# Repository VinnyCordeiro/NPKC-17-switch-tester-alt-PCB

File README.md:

# NPKC 17 Switch Tester alternative PCB
Alternative PCB to convert the NPKC 17 switch tester (https://www.massdrop.com/buy/npkc-switch-tester?mode=guest_open or https://www.massdrop.com/buy/npkc-17-switch-tester?mode=guest_open) into a number pad. It is small enough to be modified by the free version of [EAGLE](https://cadsoft.io/). You can buy the PCB through [Dirty PCBs](https://dirtypcbs.com/store/designer/details/9479/676/aunk-numpad).

The Atmel ATmega32U2 microcontroller can be programmed with both [TMK keyboard firmware](https://github.com/tmk/tmk_keyboard) and [QMK keyboard firmware](https://github.com/qmk/qmk_firmware). TMK code for this PCB can be found [here](https://github.com/VinnyCordeiro/tmk_keyboard/tree/master/keyboard/AUNK_Numpad), while the QMK code (and a standard number pad firmware) is now available here.

As of September 08, 2020, the design is still untested.

Updates
-------
#### 13/September/2016
Initial release. Included are all custom libraries for EAGLE.

#### 15/January/2019
Uploaded a tentative firmware made with the help of [Keyboard Firmware Builder](https://kbfirmware.com/). Design still untested.

#### 08/September/2020
Remebered to add the link for people to buy the PCB. Design still untested (I'm off from the mechanical keyboards hobby for personal reasons).

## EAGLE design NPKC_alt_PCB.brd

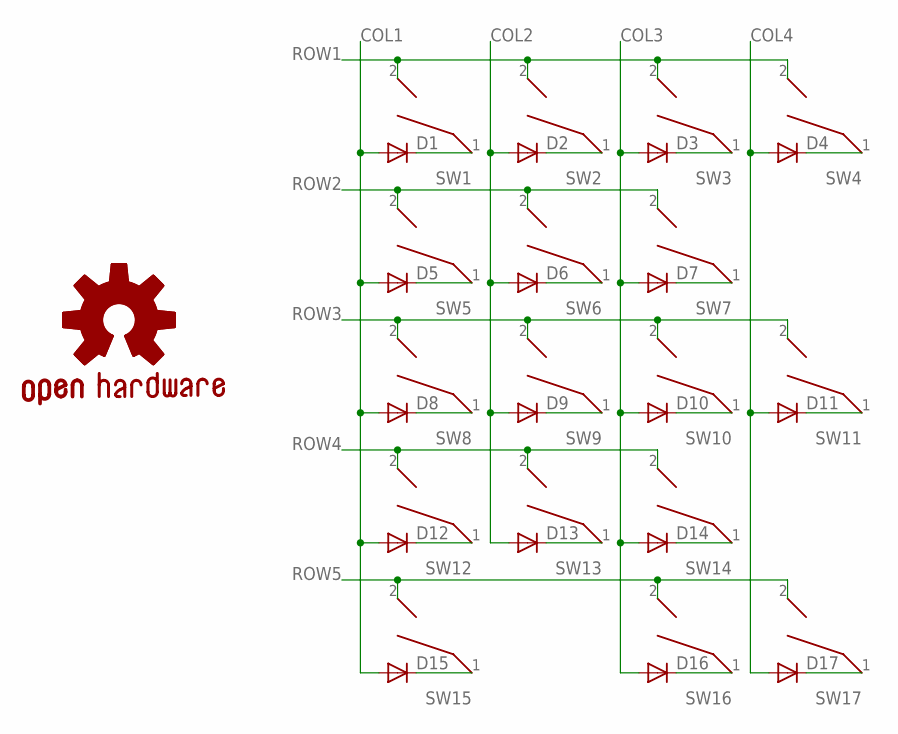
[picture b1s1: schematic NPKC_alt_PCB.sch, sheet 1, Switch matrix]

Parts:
D1, D2, D3, D4, D5, D6, D7, D8, D9, D10, D11, D12, D13, D14, D15, D16, D17: CGRM4001-G; SOD-123_MINI-SMA
GOLD_ORB_SM1: OSHWLOGO_GOLD_ORB_SM; OSHW2
SW1: Num_Lock; MX1A-XXNW
SW2: NP_/; MX1A-XXNW
SW3: NP_*; MX1A-XXNW
SW4: NP_-; MX1A-XXNW
SW5: NP_7; MX1A-XXNW
SW6: NP_8; MX1A-XXNW
SW7: NP_9; MX1A-XXNW
SW8: NP_4; MX1A-XXNW
SW9: NP_5; MX1A-XXNW
SW10: NP_6; MX1A-XXNW
SW11: NP_+; MX1A-XXNW
SW12: NP_1; MX1A-XXNW
SW13: NP_2; MX1A-XXNW
SW14: NP_3; MX1A-XXNW
SW15: NP_0; MX1A-XXNW
SW16: NP_.; MX1A-XXNW
SW17: NP_Enter; MX1A-XXNW

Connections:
COL1: D1.A, D5.A, D8.A, D12.A, D15.A; also elsewhere on the board
COL2: D2.A, D6.A, D9.A, D13.A; also elsewhere on the board
COL3: D3.A, D7.A, D10.A, D14.A, D16.A; also elsewhere on the board
COL4: D4.A, D11.A, D17.A; also elsewhere on the board
unnamed: D1.C, SW1.1
unnamed: D2.C, SW2.1
unnamed: D3.C, SW3.1
unnamed: D4.C, SW4.1
unnamed: D5.C, SW5.1
unnamed: D6.C, SW6.1
unnamed: D7.C, SW7.1
unnamed: D8.C, SW8.1
unnamed: D9.C, SW9.1
unnamed: D10.C, SW10.1
unnamed: D11.C, SW11.1
unnamed: D12.C, SW12.1
unnamed: D13.C, SW13.1
unnamed: D14.C, SW14.1
unnamed: D15.C, SW15.1
unnamed: D16.C, SW16.1
unnamed: D17.C, SW17.1
ROW1: SW1.2, SW2.2, SW3.2, SW4.2; also elsewhere on the board
ROW2: SW5.2, SW6.2, SW7.2; also elsewhere on the board
ROW3: SW8.2, SW9.2, SW10.2, SW11.2; also elsewhere on the board
ROW4: SW12.2, SW13.2, SW14.2; also elsewhere on the board
ROW5: SW15.2, SW16.2, SW17.2; also elsewhere on the board

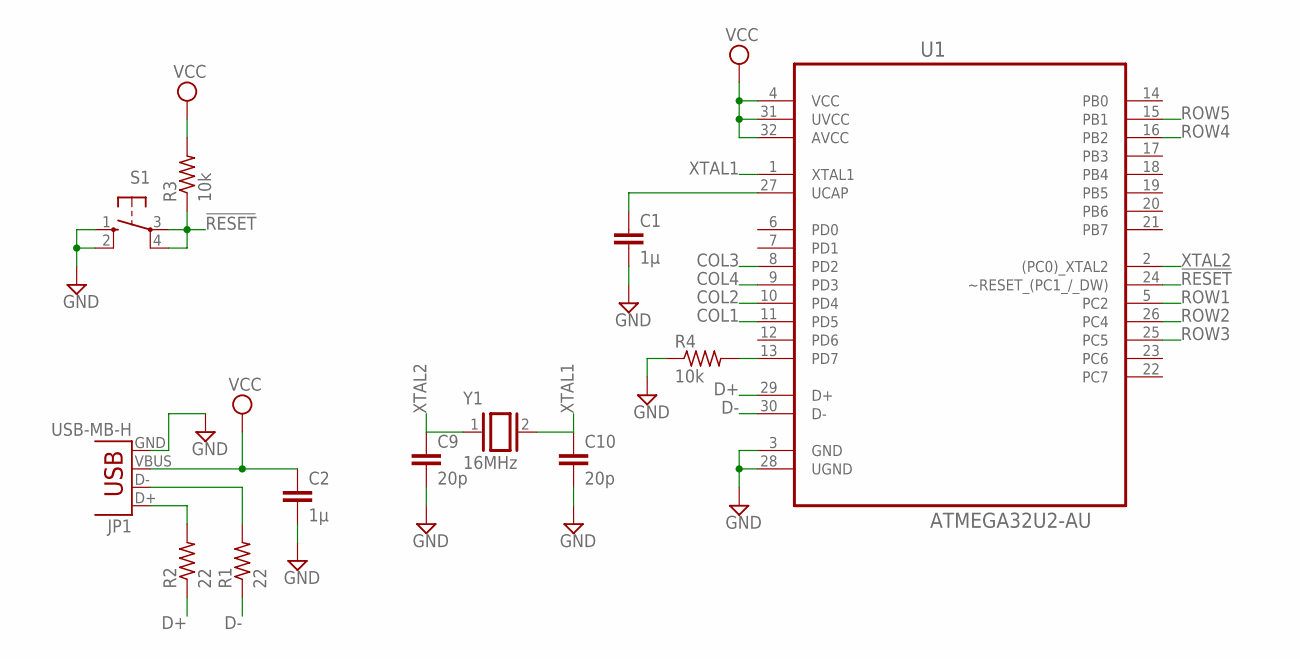
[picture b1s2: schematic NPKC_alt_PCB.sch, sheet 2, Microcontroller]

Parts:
C1: 1µ; C0805K
C2: 1µ; C0805
C9, C10: 20p; C0805K
JP1: USB-MB-H
R1, R2: 22; R0805
R3, R4: 10k; R0805
S1: 10-XX; B3F-10XX
U1: ATMEGA32U2-AU; QFP80P900X900X120-32N
Y1: 16MHz; QS

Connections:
!RESET!: R3.1, S1.3, S1.4 (P1), U1.24 (~RESET_(PC1_/_DW))
COL1: U1.11 (PD5); also elsewhere on the board
COL2: U1.10 (PD4); also elsewhere on the board
COL3: U1.8 (PD2); also elsewhere on the board
COL4: U1.9 (PD3); also elsewhere on the board
D+: R2.1, U1.29 (D+)
D-: R1.1, U1.30 (D-)
GND: C1.2, C2.2, C9.2, C10.2, JP1.GND, R4.1, S1.1 (S), S1.2 (S1), U1.3 (GND), U1.28 (UGND)
unnamed: C1.1, U1.27 (UCAP)
unnamed: R4.2, U1.13 (PD7)
unnamed: JP1.D+, R2.2
unnamed: JP1.D-, R1.2
ROW1: U1.5 (PC2); also elsewhere on the board
ROW2: U1.26 (PC4); also elsewhere on the board
ROW3: U1.25 (PC5); also elsewhere on the board
ROW4: U1.16 (PB2); also elsewhere on the board
ROW5: U1.15 (PB1); also elsewhere on the board
VCC: C2.1, JP1.VBUS, R3.2, U1.4 (VCC), U1.31 (UVCC), U1.32 (AVCC)
XTAL1: C10.1, U1.1 (XTAL1), Y1.2
XTAL2: C9.1, U1.2 ((PC0)_XTAL2), Y1.1

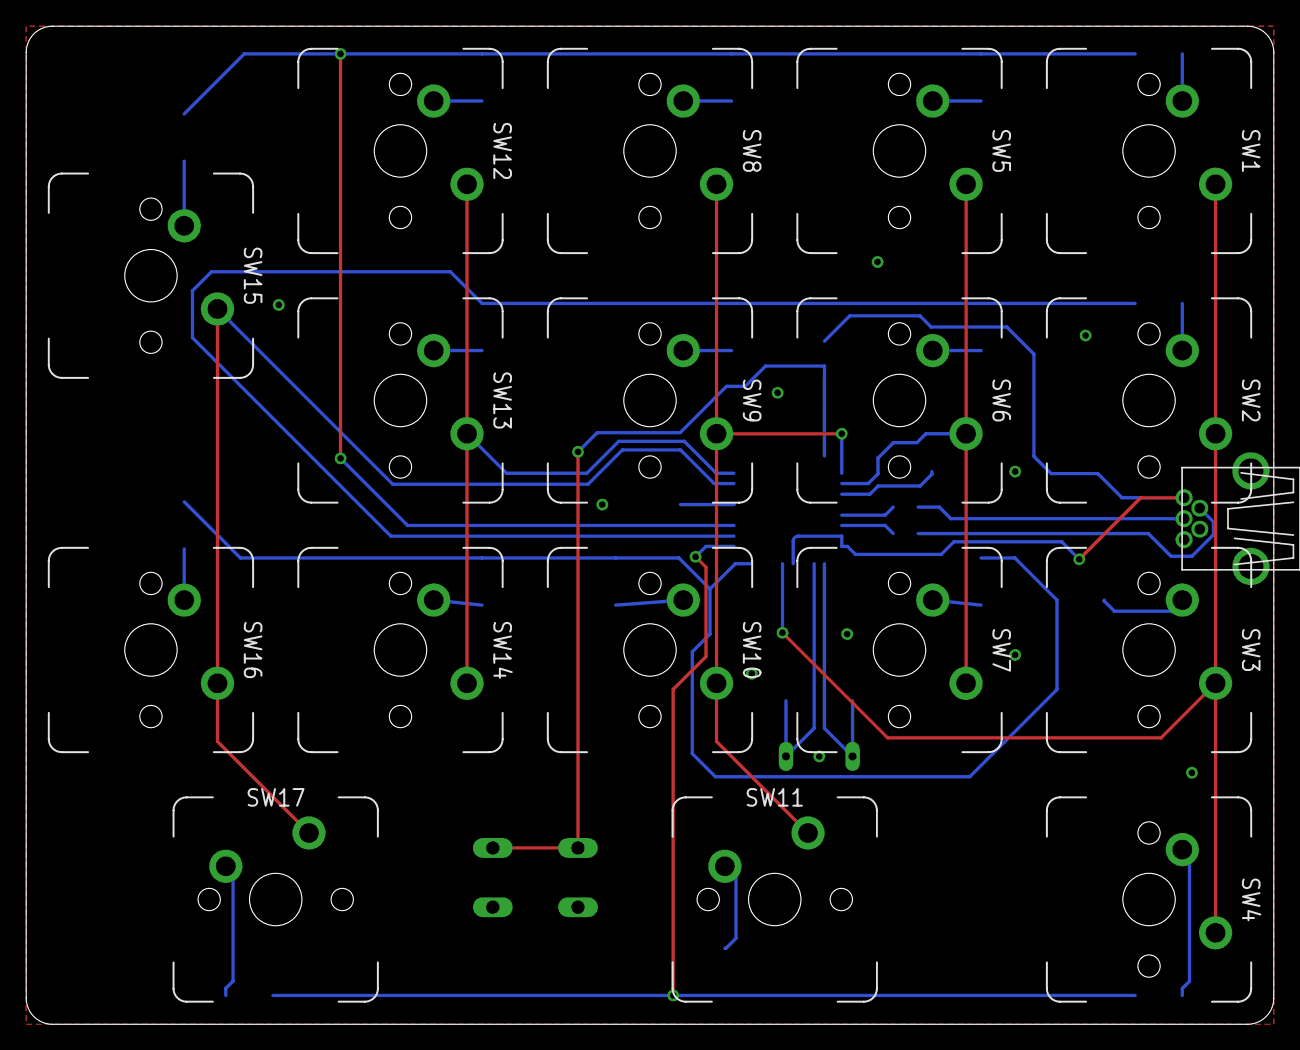
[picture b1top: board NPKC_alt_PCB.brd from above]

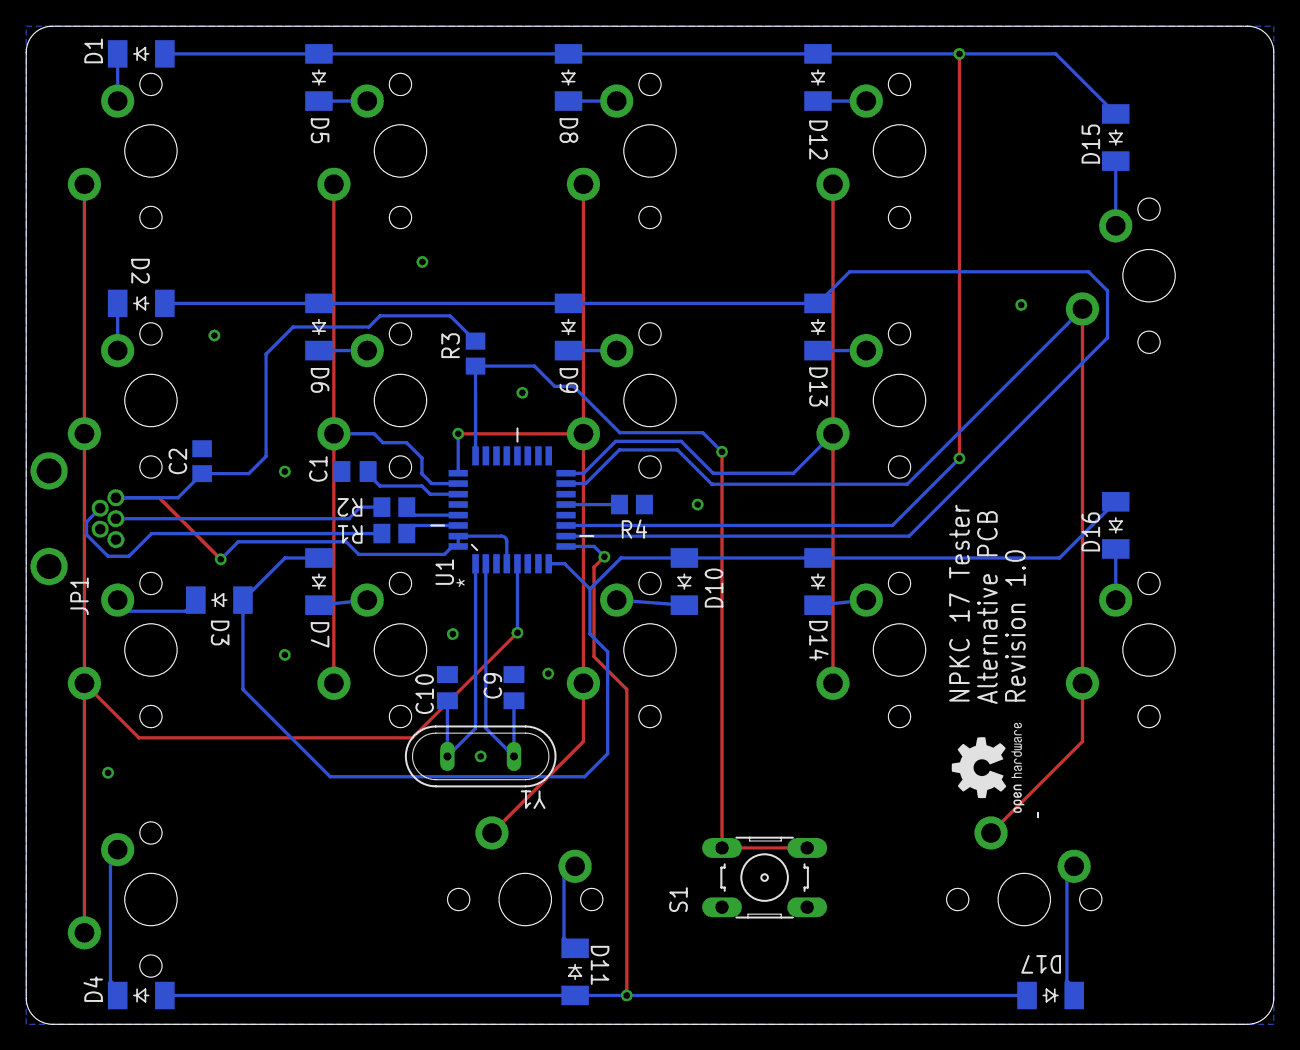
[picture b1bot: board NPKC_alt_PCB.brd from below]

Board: 2 copper layers, 95.2 x 76.2 mm, 47 parts (30 on the bottom side), 37 nets.

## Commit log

2016-09-13 Update LICENSE
2016-09-13 2016/09/13: Initial release.
2018-07-16 Update LICENSE
    Changed from a modified MIT License (which probably wouldn't be valid anyway) to the CERN Open Hardware Licence v1.2
2019-01-15 Tentative firmware uploaded
    Made with the help of Keyboard Firmware Builder - https://kbfirmware.com/; untested so far.
2019-01-15 Update README.md
    Included information about QMK firmware and updated the warning about the design still being untested.

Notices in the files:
parts and their libraries:
SparkFun-Connectors: Licensing: Creative Commons ShareAlike 4.0 International - https://creativecommons.org/licenses/by-sa/4.0
